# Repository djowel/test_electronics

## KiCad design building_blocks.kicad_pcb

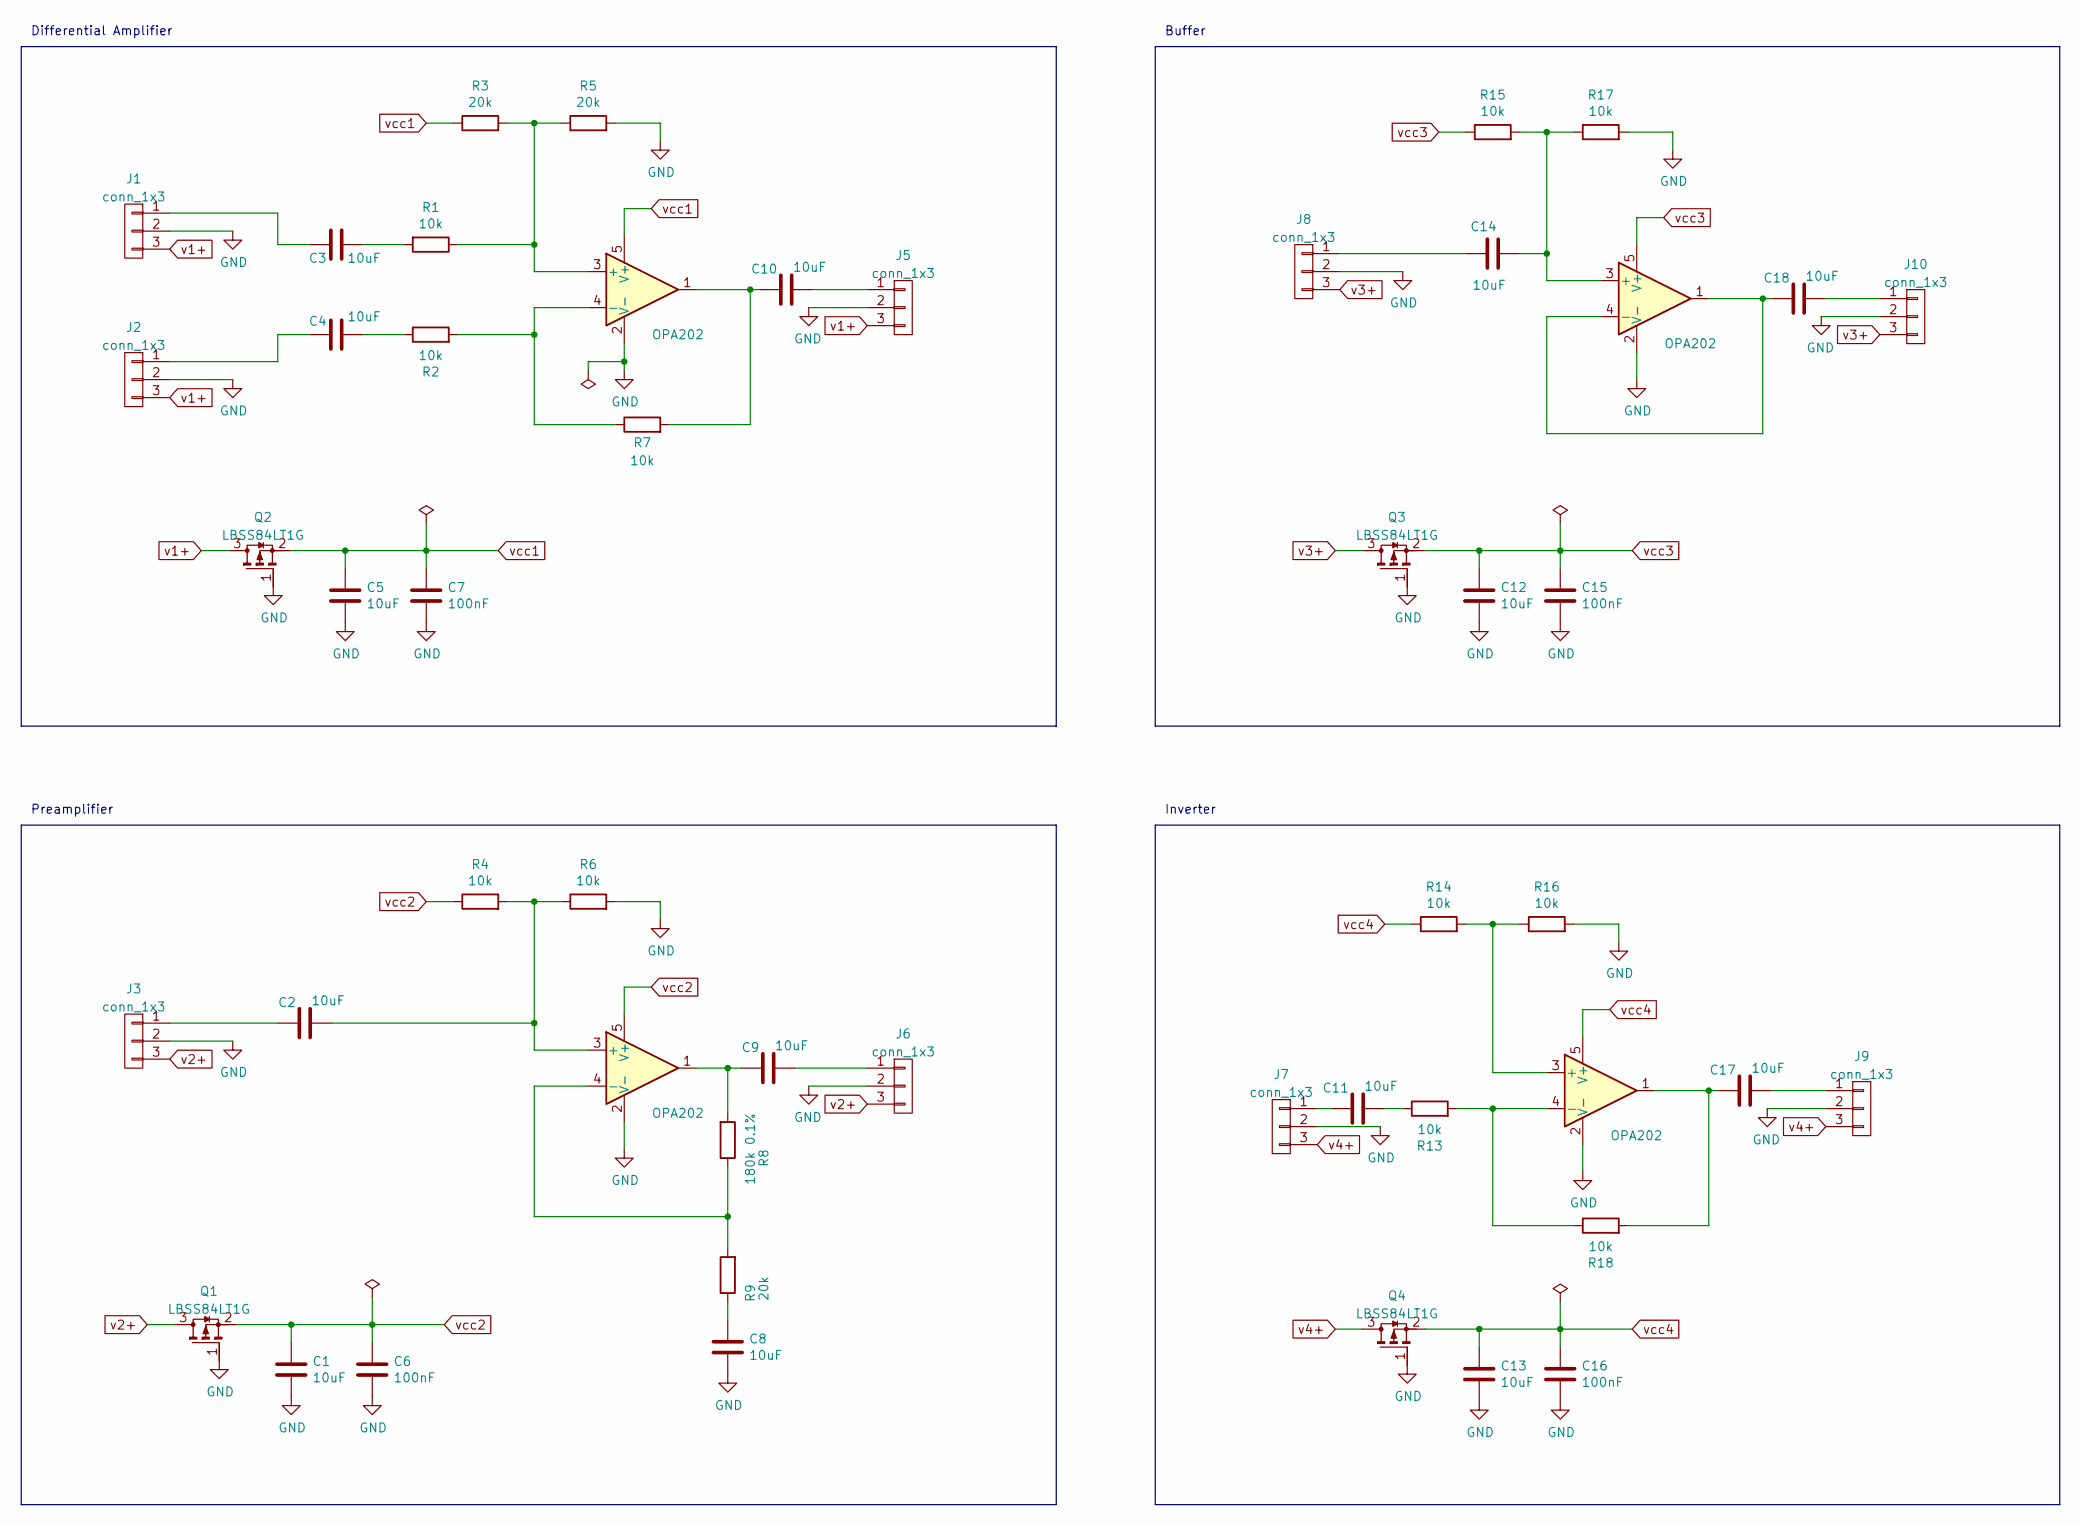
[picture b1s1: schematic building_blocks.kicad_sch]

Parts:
C1, C2, C3, C4, C5, C8, C9, C10, C11, C12, C13, C14, C17, C18: 10uF; C_0805_2012Metric; LCSC C15850
C6, C7, C15, C16: 100nF; C_0402_1005Metric; LCSC C307331
J1, J2, J3, J5, J6, J7, J8, J9, J10: conn_1x3; pin_header_1x3p_2.54mm_smd_horizontal
Q1, Q2, Q3, Q4: LBSS84LT1G; TSOT-23; LCSC C8492
R1, R2, R4, R6, R7, R13, R14, R15, R16, R17, R18: 10k; R_0402_1005Metric; LCSC C25744
R3, R5, R9: 20k; R_0402_1005Metric; LCSC C25765
R8: 180k 0.1%; R_0603_1608Metric; LCSC C326731
U1, U2, U3, U4: OPA202; SOT-23-5; LCSC C1850244

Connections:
GND: C1.2, C5.2, C6.2, C7.2, C8.2, C12.2, C13.2, C15.2, C16.2, J1.2, J2.2, J3.2, J5.2, J6.2, J7.2, J8.2, J9.2, J10.2, Q1.1 (G), Q2.1 (G), Q3.1 (G), Q4.1 (G), R5.2, R6.2, R16.2, R17.2, U1.2 (V-), U2.2 (V-), U3.2 (V-), U4.2 (V-)
unnamed: C2.1, J3.1
unnamed: C2.2, R4.2, R6.1, U2.3 (+)
unnamed: C3.1, J1.1
unnamed: C3.2, R1.2
unnamed: C4.1, J2.1
unnamed: C4.2, R2.1
unnamed: C8.1, R9.1
unnamed: C9.1, R8.2, U2.1
unnamed: C9.2, J6.1
unnamed: C10.1, R7.2, U1.1
unnamed: C10.2, J5.1
unnamed: C11.1, J7.1
unnamed: C11.2, R13.1
unnamed: C14.1, J8.1
unnamed: C14.2, R15.2, R17.1, U4.3 (+)
unnamed: C17.1, R18.2, U3.1
unnamed: C17.2, J9.1
unnamed: C18.1, U4.1, U4.4 (-)
unnamed: C18.2, J10.1
unnamed: R1.1, R3.2, R5.1, U1.3 (+)
unnamed: R2.2, R7.1, U1.4 (-)
unnamed: R8.1, R9.2, U2.4 (-)
unnamed: R13.2, R18.1, U3.4 (-)
unnamed: R14.2, R16.1, U3.3 (+)
v1+: J1.3, J2.3, J5.3, Q2.3 (D)
v2+: J3.3, J6.3, Q1.3 (D)
v3+: J8.3, J10.3, Q3.3 (D)
v4+: J7.3, J9.3, Q4.3 (D)
vcc1: C5.1, C7.1, Q2.2 (S), R3.1, U1.5 (V+)
vcc2: C1.1, C6.1, Q1.2 (S), R4.1, U2.5 (V+)
vcc3: C12.1, C15.1, Q3.2 (S), R15.1, U4.5 (V+)
vcc4: C13.1, C16.1, Q4.2 (S), R14.1, U3.5 (V+)

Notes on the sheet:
Buffer
Inverter
Preamplifier
Differential Amplifier

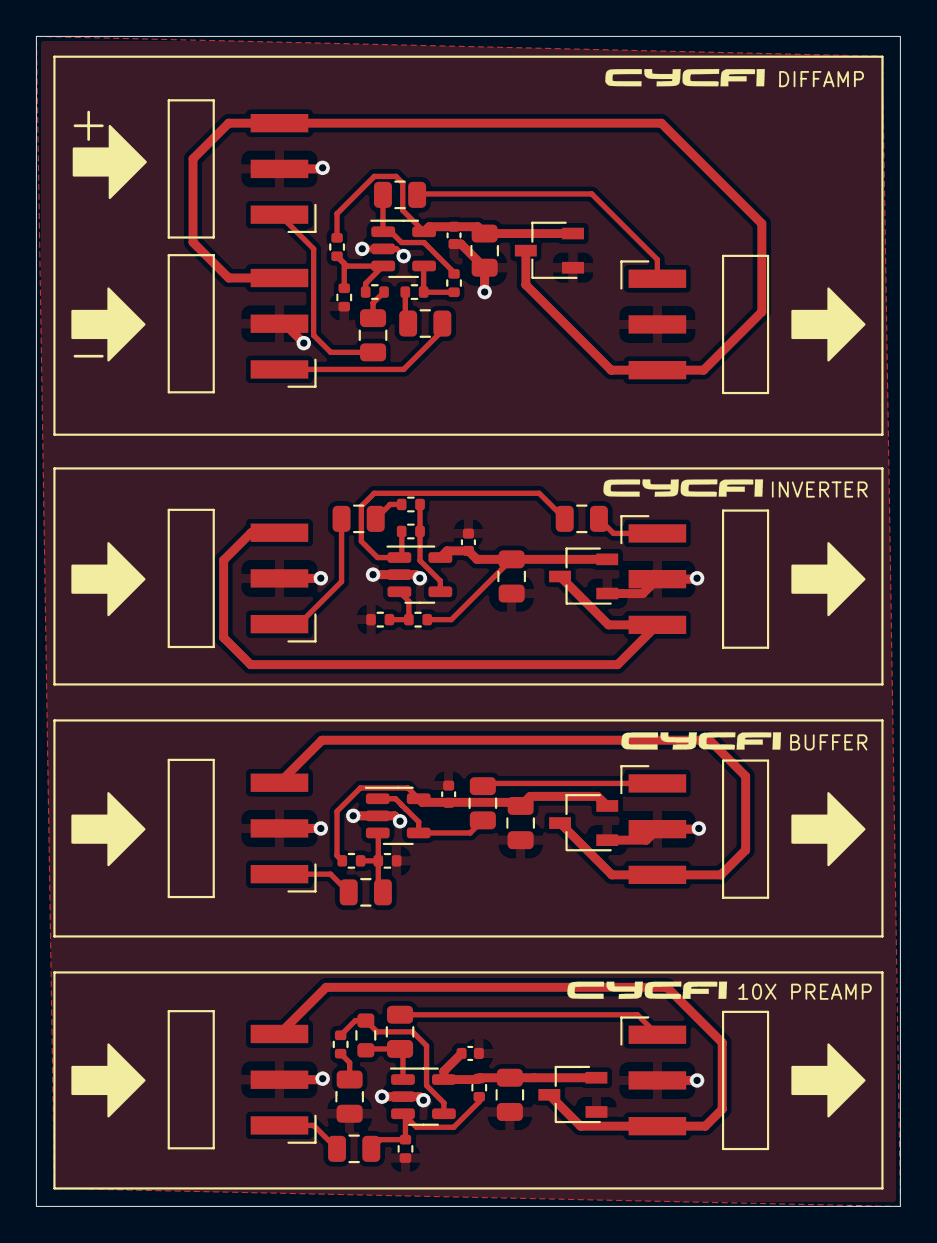
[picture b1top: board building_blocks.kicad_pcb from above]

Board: 2 copper layers, 48.0 x 65.0 mm, 50 parts (0 on the bottom side), 33 nets.

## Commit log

2024-11-01 Place all headers on top
2024-11-01 Move logo
2024-11-01 refinements
2024-11-01 More refinements
2024-11-02 Added kikit fab script
